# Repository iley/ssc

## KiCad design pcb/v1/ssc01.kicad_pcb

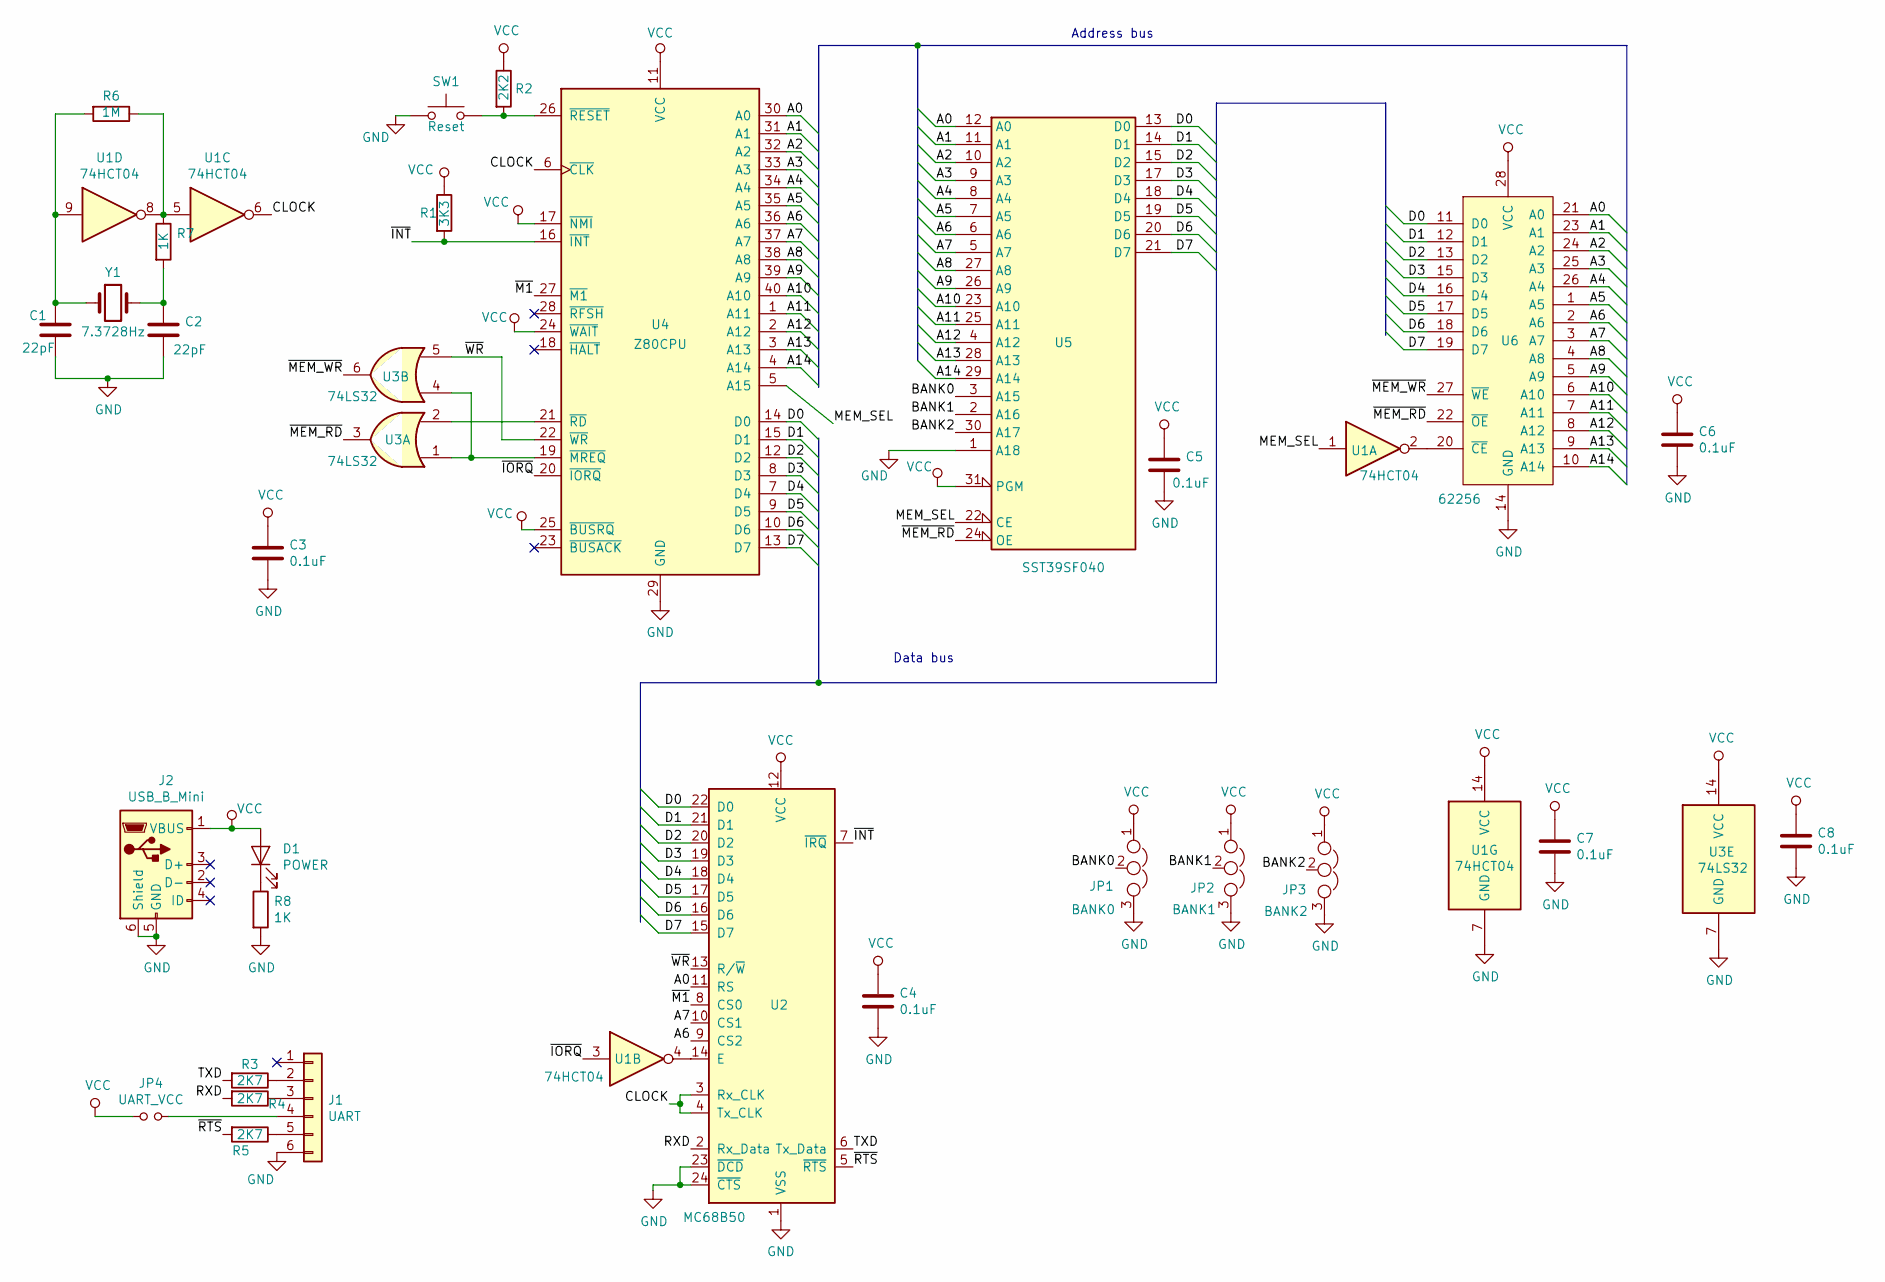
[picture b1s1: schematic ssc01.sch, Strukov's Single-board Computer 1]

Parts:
C1, C2: 22pF; C_Disc_D3.8mm_W2.6mm_P2.50mm
C3, C4, C5, C6, C7, C8: 0.1uF; C_Disc_D3.8mm_W2.6mm_P2.50mm
D1: POWER; LED_1206_3216Metric
J1: UART; PinHeader_1x06_P2.54mm_Vertical
J2: USB_B_Mini; USB_Mini-B_Lumberg_2486_01_Horizontal
JP1: BANK0; PinHeader_1x03_P2.54mm_Vertical
JP2: BANK1; PinHeader_1x03_P2.54mm_Vertical
JP3: BANK2; PinHeader_1x03_P2.54mm_Vertical
JP4: UART_VCC; PinHeader_1x02_P2.54mm_Vertical
R1: 3K3; R_Axial_DIN0207_L6.3mm_D2.5mm_P10.16mm_Horizontal
R2: 2K2; R_Axial_DIN0207_L6.3mm_D2.5mm_P10.16mm_Horizontal
R3, R4, R5: 2K7; R_Axial_DIN0207_L6.3mm_D2.5mm_P10.16mm_Horizontal
R6: 1M; R_Axial_DIN0207_L6.3mm_D2.5mm_P10.16mm_Horizontal
R7, R8: 1K; R_Axial_DIN0207_L6.3mm_D2.5mm_P10.16mm_Horizontal
SW1: Reset; SW_PUSH_6mm
U1: 74HCT04; DIP-14_W7.62mm_LongPads
U2: MC68B50; DIP-24_W15.24mm_LongPads
U3: 74LS32; DIP-14_W7.62mm_LongPads
U4: Z80CPU; DIP-40_W15.24mm_Socket_LongPads
U5: SST39SF040; DIP-32_W15.24mm_LongPads
U6: 62256; DIP-28_W15.24mm_LongPads
Y1: 7.3728Hz; Crystal_HC49-4H_Vertical

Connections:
/A0: U2.11 (RS), U4.30 (A0), U5.12 (A0), U6.21 (A0)
/A1: U4.31 (A1), U5.11 (A1), U6.23 (A1)
/A2: U4.32 (A2), U5.10 (A2), U6.24 (A2)
/A3: U4.33 (A3), U5.9 (A3), U6.25 (A3)
/A4: U4.34 (A4), U5.8 (A4), U6.26 (A4)
/A5: U4.35 (A5), U5.7 (A5), U6.1 (A5)
/A6: U2.9 (CS2), U4.36 (A6), U5.6 (A6), U6.2 (A6)
/A7: U2.10 (CS1), U4.37 (A7), U5.5 (A7), U6.3 (A7)
/A8: U4.38 (A8), U5.27 (A8), U6.4 (A8)
/A9: U4.39 (A9), U5.26 (A9), U6.5 (A9)
/A10: U4.40 (A10), U5.23 (A10), U6.6 (A10)
/A11: U4.1 (A11), U5.25 (A11), U6.7 (A11)
/A12: U4.2 (A12), U5.4 (A12), U6.8 (A12)
/A13: U4.3 (A13), U5.28 (A13), U6.9 (A13)
/A14: U4.4 (A14), U5.29 (A14), U6.10 (A14)
/BANK0: JP1.2, U5.3 (A15)
/BANK1: JP2.2, U5.2 (A16)
/BANK2: JP3.2, U5.30 (A17)
/CLOCK: U1.6, U2.3 (Rx_CLK), U2.4 (Tx_CLK), U4.6 (~CLK~)
/D0: U2.22 (D0), U4.14 (D0), U5.13 (D0), U6.11 (D0)
/D1: U2.21 (D1), U4.15 (D1), U5.14 (D1), U6.12 (D1)
/D2: U2.20 (D2), U4.12 (D2), U5.15 (D2), U6.13 (D2)
/D3: U2.19 (D3), U4.8 (D3), U5.17 (D3), U6.15 (D3)
/D4: U2.18 (D4), U4.7 (D4), U5.18 (D4), U6.16 (D4)
/D5: U2.17 (D5), U4.9 (D5), U5.19 (D5), U6.17 (D5)
/D6: U2.16 (D6), U4.10 (D6), U5.20 (D6), U6.18 (D6)
/D7: U2.15 (D7), U4.13 (D7), U5.21 (D7), U6.19 (D7)
/MEM_SEL: U1.1, U4.5 (A15), U5.22 (CE)
/RXD: R4.2, U2.2 (Rx_Data)
/TXD: R3.2, U2.6 (Tx_Data)
/~INT: R1.2, U2.7 (~IRQ), U4.16 (~INT~)
/~IORQ: U1.3, U4.20 (~IORQ~)
/~M1: U2.8 (CS0), U4.27 (~M1~)
/~MEM_RD: U3.3, U5.24 (OE), U6.22 (~OE)
/~MEM_WR: U3.6, U6.27 (~WE)
/~RTS: R5.2, U2.5 (~RTS)
/~WR: U2.13 (R/~W), U3.5, U4.22 (~WR~)
GND: C1.2, C2.2, C3.2, C4.2, C5.2, C6.2, C7.2, C8.2, J1.6, J2.5 (GND), J2.6 (Shield), JP1.3, JP2.3, JP3.3, R8.2, SW1.1, U1.7 (GND), U2.1 (VSS), U2.23 (~DCD), U2.24 (~CTS), U3.7 (GND), U4.29 (GND), U5.1 (A18), U5.16 (GND), U6.14 (GND)
unnamed: C1.1, R6.2, U1.9, Y1.1
unnamed: C2.1, R7.2, Y1.2
unnamed: D1.1 (K), R8.1
unnamed: J1.2, R3.1
unnamed: J1.3, R4.1
unnamed: J1.4, JP4.2
unnamed: J1.5, R5.1
unnamed: R2.2, SW1.2, U4.26 (~RESET~)
unnamed: R6.1, R7.1, U1.5, U1.8
unnamed: U1.2, U6.20 (~CE)
unnamed: U1.4, U2.14 (E)
unnamed: U3.1, U3.4, U4.19 (~MREQ~)
unnamed: U3.2, U4.21 (~RD~)
VCC: C3.1, C4.1, C5.1, C6.1, C7.1, C8.1, D1.2 (A), J2.1 (VBUS), JP1.1, JP2.1, JP3.1, JP4.1, R1.1, R2.1, U1.14 (VCC), U2.12 (VCC), U3.14 (VCC), U4.11 (VCC), U4.17 (~NMI~), U4.24 (~WAIT~), U4.25 (~BUSRQ~), U5.31 (PGM), U5.32 (VCC), U6.28 (VCC)

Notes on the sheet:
Data bus
Address bus

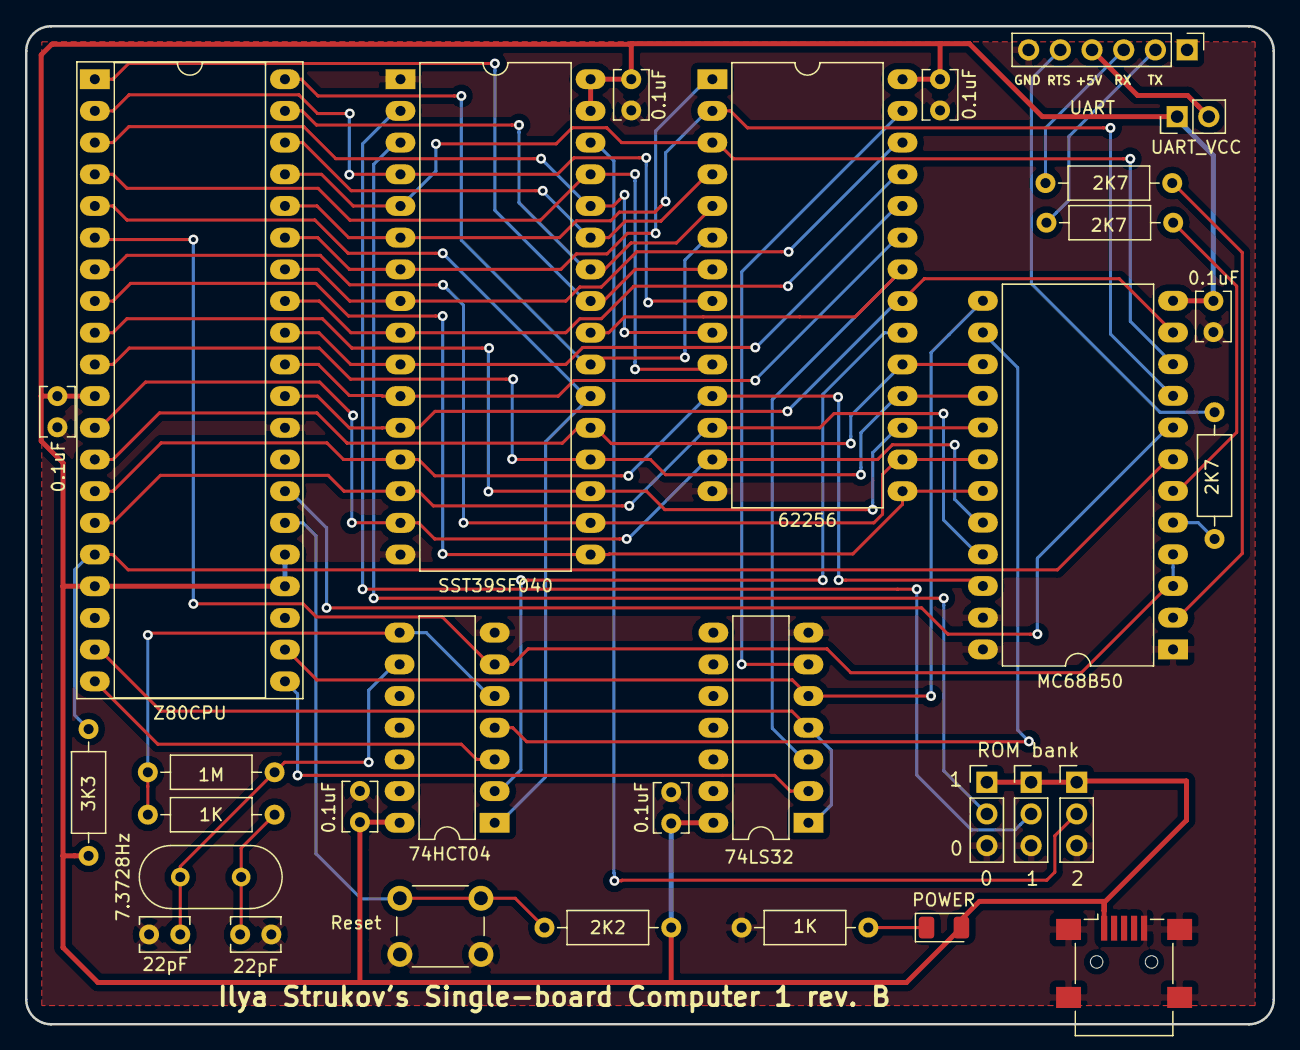
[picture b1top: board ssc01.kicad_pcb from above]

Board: 2 copper layers, 100.0 x 80.0 mm, 31 parts (0 on the bottom side), 52 nets.

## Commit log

2019-01-01 start the schematic
2019-01-01 start wiring RAM and ROM
2019-01-01 draw most of the schematic
2019-01-01 finish first draft of a schematic
2019-01-01 minor pcb changes
2019-01-02 power and bypass caps
2019-01-03 start the layout
2019-01-05 continue layout
2019-01-05 complete layout
2019-01-06 layout in progress
2019-01-06 second take at the layout
2019-01-06 finish second layout iteration
2019-01-06 final touches
2019-01-19 replace the MC68B50 footprint
2019-01-19 move some tracks
2020-10-11 Update KiCAD files
